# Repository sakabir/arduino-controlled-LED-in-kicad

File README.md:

# arduino-controlled-LED-in-kicad

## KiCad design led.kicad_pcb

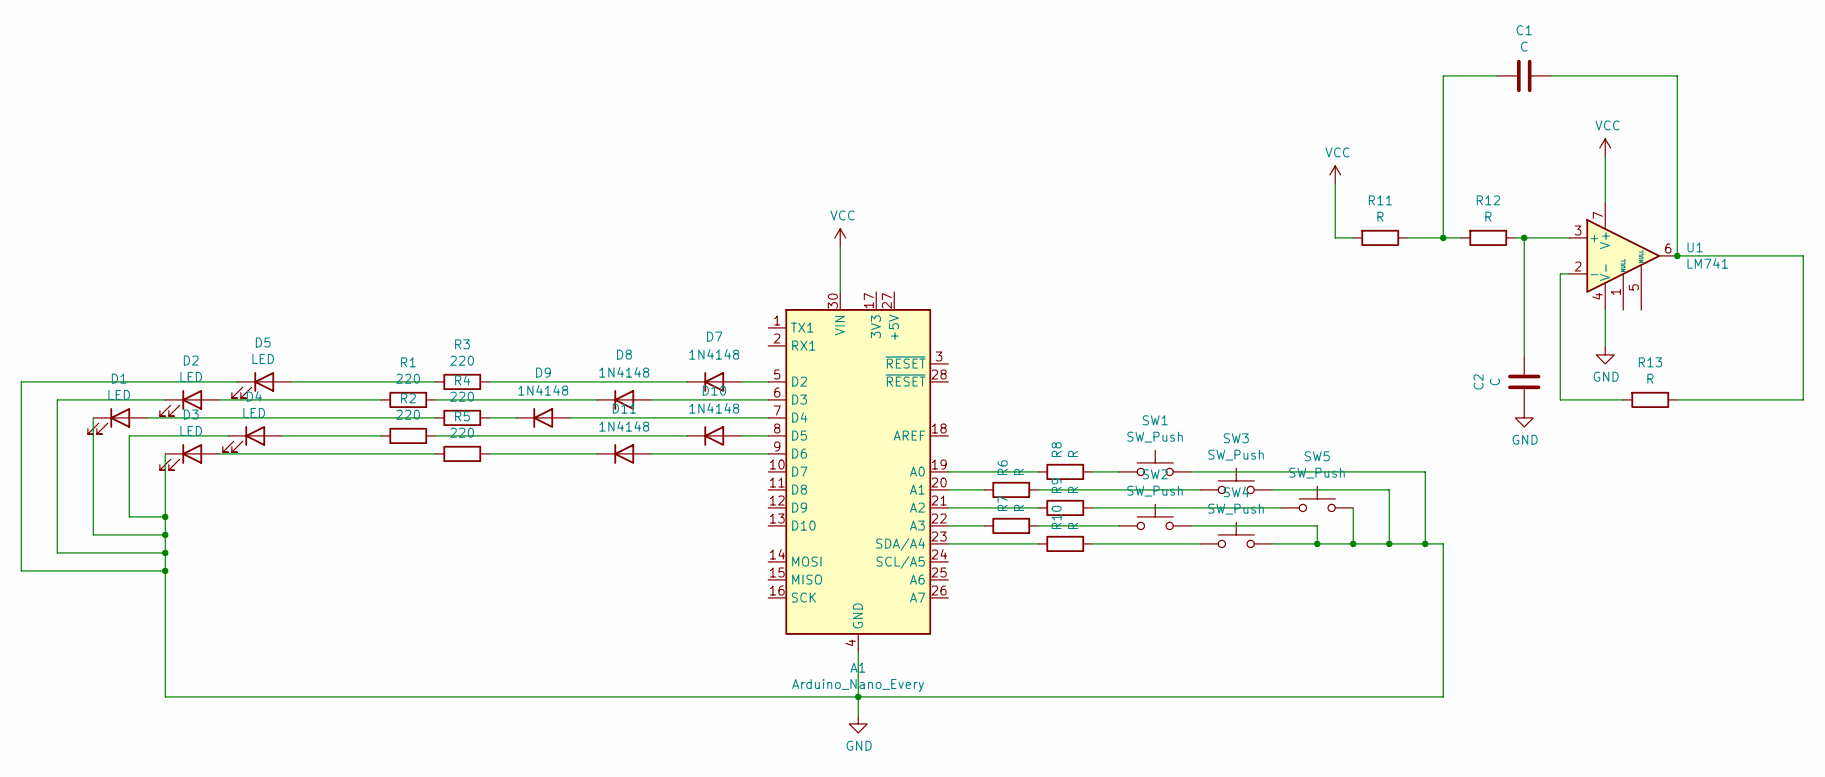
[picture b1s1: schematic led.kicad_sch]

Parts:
A1: Arduino_Nano_Every; Arduino_Nano_WithMountingHoles
C1, C2: C; CP_Axial_L10.0mm_D4.5mm_P15.00mm_Horizontal
D1, D2, D3, D4, D5: LED; LED_D3.0mm_FlatTop
D7, D8, D9, D10, D11: 1N4148; D_DO-35_SOD27_P7.62mm_Horizontal
R1, R2, R3, R4, R5: 220; R_Axial_DIN0204_L3.6mm_D1.6mm_P5.08mm_Horizontal
R6, R7, R8, R9, R10, R11, R12, R13: R; R_Axial_DIN0204_L3.6mm_D1.6mm_P5.08mm_Horizontal
SW1, SW2, SW3, SW4, SW5: SW_Push; KSA_Tactile_SPST
U1: LM741; DIP-8-16_W7.62mm

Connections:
GND: A1.4 (GND), A1.29 (GND), C2.2, D1.1 (K), D2.1 (K), D3.1 (K), D4.1 (K), D5.1 (K), SW1.2, SW2.2, SW3.2, SW4.2, SW5.2, U1.4 (V-)
unnamed: A1.19 (A0), R8.1
unnamed: A1.20 (A1), R6.1
unnamed: A1.21 (A2), R9.1
unnamed: A1.22 (A3), R7.1
unnamed: A1.5 (D2), D7.2 (A)
unnamed: A1.6 (D3), D8.2 (A)
unnamed: A1.7 (D4), D9.2 (A)
unnamed: A1.8 (D5), D10.2 (A)
unnamed: A1.9 (D6), D11.2 (A)
unnamed: A1.23 (SDA/A4), R10.1
unnamed: C1.1, R13.1, U1.6
unnamed: C1.2, R11.1, R12.2
unnamed: D1.2 (A), R4.1
unnamed: D2.2 (A), R1.1
unnamed: D3.2 (A), R5.1
unnamed: D4.2 (A), R2.1
unnamed: D5.2 (A), R3.1
unnamed: D7.1 (K), R3.2
unnamed: D8.1 (K), R1.2
unnamed: D9.1 (K), R4.2
unnamed: D10.1 (K), R2.2
unnamed: D11.1 (K), R5.2
unnamed: R6.2, SW3.1
unnamed: R7.2, SW2.1
unnamed: R8.2, SW1.1
unnamed: R9.2, SW5.1
unnamed: R10.2, SW4.1
unnamed: C2.1, R12.1, U1.3 (+)
unnamed: R13.2, U1.2 (-)
VCC: A1.30 (VIN), R11.2, U1.7 (V+)

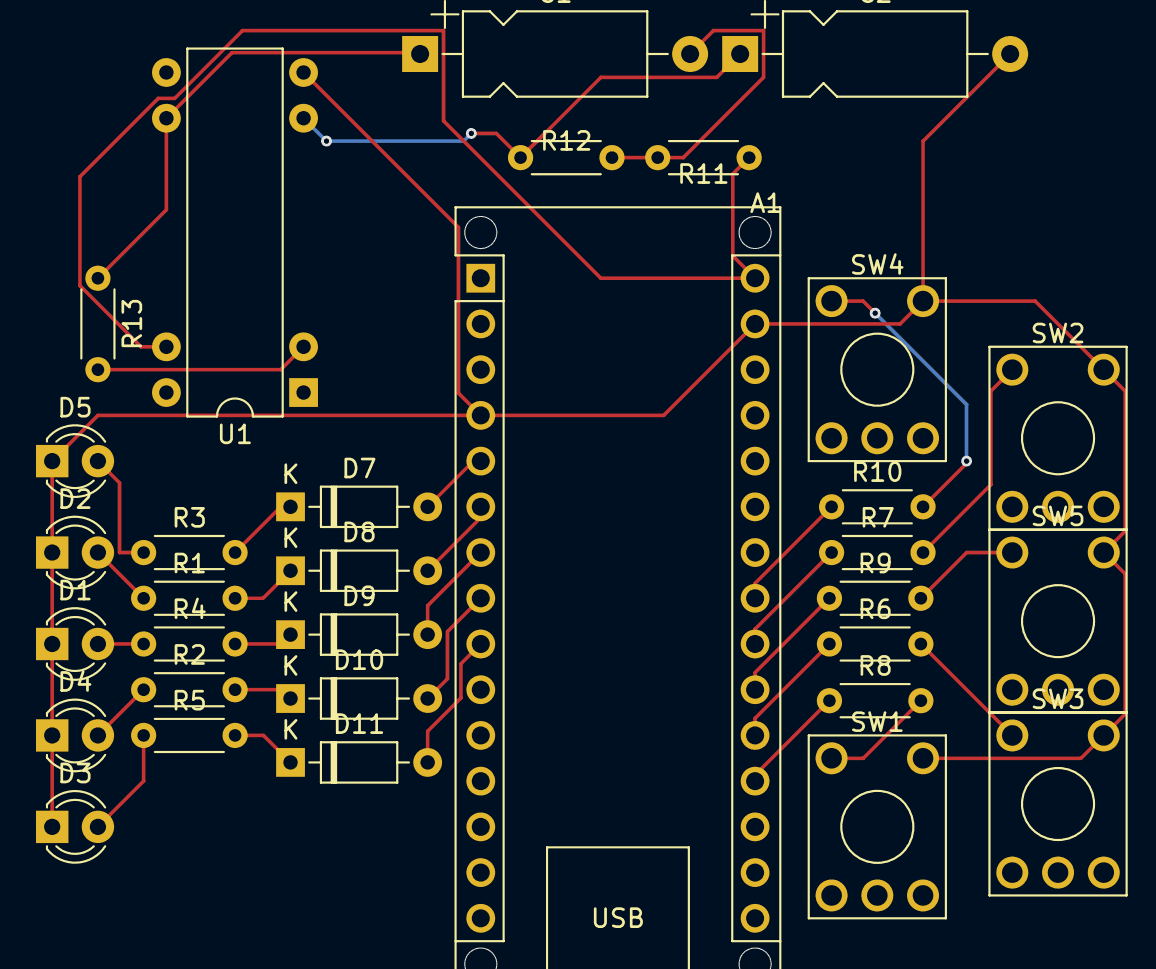
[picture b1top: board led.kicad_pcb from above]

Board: 2 copper layers, 32 parts (0 on the bottom side), 31 nets.
